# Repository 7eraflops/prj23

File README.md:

# 3-Phase 12-Channel ESP32 Energy Monitor

A custom ESP32-based energy meter measuring up to 12 channels across a 3-phase supply, integrated with Home Assistant via MQTT.

## Current Status
- End-to-end firmware flow is working on ESP32 DevKit: provisioning -> Wi-Fi -> MQTT -> HA discovery -> telemetry -> command handling.
- ATM90E32 real driver path is implemented (`register map`, `SPI transport`, `ATM90E32Sensor` implementing `IEnergySensor`).
- DevKit-only mock-IC path is implemented on a dedicated testing branch.
- Custom PCB and physical calibration are pending hardware availability.

## Overview
- **Measurement**: Uses the ATM90E32AS metering IC to monitor up to 12 circuits (11 used in current planned deployment).
- **Microcontroller**: ESP32-S3.
- **Integration**: Home Assistant MQTT Auto-Discovery for automatic entity configuration.
- **Provisioning**: Local captive portal and web server for Wi-Fi and MQTT setup.
- **Testing**: Uses mock sensor paths for software development before final hardware is available.

## Hardware
- **Custom PCB**: Currently in development.
- **MCU**: ESP32-S3
- **Metering IC**: ATM90E32AS
- **Sensors**: Current Transformers (CT Clamps) and Voltage Dividers

## Firmware Architecture
- `config_manager`: NVS-backed configuration (Wi-Fi, MQTT, channel phase assignment, active mask, calibration groundwork)
- `wifi_manager`: station lifecycle and reconnection
- `mqtt_manager`: client lifecycle, subscribe/publish, callback handling
- `ha_discovery`: Home Assistant discovery payload publishing
- `command_handler`: command topic handling and runtime config updates
- `sensor_manager`: polling task and telemetry publishing loop
- `atm90e32_interface`: register definitions, SPI transport, device abstraction
- `web_server`: provisioning/config pages and OTA endpoint

## Software Stack
- **Framework**: ESP-IDF (C/C++)
- **RTOS**: FreeRTOS
- **Communication**: MQTT (Mosquitto), HTTP (Local Web Server)
- **Data Processing**: Non-Intrusive Load Monitoring (NILM) runs server-side (Home Assistant / Raspberry Pi), not on the ESP32.

---

## Project Roadmap

### Phase 1: Software Foundation & HA Integration (Completed)
*Goal: Build the end-to-end data pipeline on the DevKit using mocked data before the physical hardware arrives.*

- [x] **Config & Provisioning (`config_manager`, `web_setup`)**
  - Save/load Wi-Fi and MQTT credentials using NVS.
  - Initial captive portal for device provisioning.
- [x] **MQTT Manager (`mqtt_manager`)**
  - Implement `esp_mqtt_client` using credentials from `config_manager`.
  - Handle connect/disconnect events and auto-reconnection logic.
- [x] **Home Assistant Auto-Discovery (`ha_discovery`)**
  - Implement HA MQTT Auto-Discovery protocol.
  - Publish JSON configuration payloads for Voltage, Current, Active Power, etc.
- [x] **Hardware Abstraction & Mock Sensor (`sensor_manager`)**
  - Define a generic sensor interface (`IEnergySensor`).
  - Create a `DummyEnergySensor` that generates fluctuating test data.
  - Implement a FreeRTOS telemetry task to poll the sensor and publish JSON payloads.

### Phase 2: Pre-Hardware System Features (Mostly Completed)
*Goal: Implement system-level features that can be tested on an ESP32 dev board before the custom PCBs arrive.*

- [x] **Continuous Web Server**
  - Keep web server active on the local network post-provisioning.
- [x] **Over-The-Air (OTA) Updates**
  - Implement OTA flashing mechanism.
  - Add an `/update` endpoint to the local web server to allow uploading firmware binaries.
- [x] **Two-Way MQTT Communication (Device Control)**
  - Add Home Assistant "Button" entities via HA Discovery (e.g., "Reboot").
  - Subscribe to command topics in `mqtt_manager` and execute device actions.
- [x] **Calibration Storage Groundwork**
  - Add NVS fields in `config_manager` for per-channel calibration settings.
- [X] **Calibration Web UI**
  - Add a `/calibration` web page to view and edit multipliers dynamically.

### Phase 3: Hardware Driver Preparation (In Progress)
*Goal: Write and validate the ATM90E32AS SPI driver path before custom hardware arrives.*

- [x] **ATM90E32AS Register Map**
  - Create header files defining register addresses and constants for status, calibration, instant values, power, and energy.
- [x] **SPI Interface**
  - Initialize the ESP32-S3 SPI master peripheral for shared bus + per-chip CS.
  - Implement low-level `read16()` and `write16()` functions and split-register 32-bit reads.
- [x] **ATM90E32 Sensor Implementation**
  - Create `ATM90E32Sensor` implementing `IEnergySensor`.
  - Integrate channel phase assignment and active mask behavior with existing runtime config.
- [x] **DevKit Mock IC Validation Path**
  - Add register-level ATM90E32 emulation path on testing branch to simulate fluctuating values and command/read flow.
- [ ] **Hardware Profile Finalization**
  - Finalize tuned mode/gain/threshold values when PCB and front-end are finalized.

### Phase 4: Hardware Bring-Up & Validation
*Goal: Validate the custom PCB and physically calibrate the sensors.*

- [X] **Physical Bring-Up**
  - Solder and power the PCB.
  - Validate SPI communication (e.g., read ATM90E32AS status/identity paths).
- [ ] **Live Calibration**
  - Connect actual loads and adjust multipliers via the Calibration Web UI.
  - Verify baseline noise and power factor readings.

### Phase 5: Non-Intrusive Load Monitoring (NILM)
*Goal: Differentiate multiple appliances sharing the same electrical circuit.*

#### ESP32 Responsibility (Data Provider)
The ESP32 acts as a high-fidelity data provider to Home Assistant. To aid in NILM separation, it publishes high-frequency updates (1-2 second intervals) per channel, including:
1. Active Power (W)
2. Reactive Power (var)
3. Apparent Power (VA)
4. Power Factor
5. Voltage (V) & Current (A)
6. Energy (kWh) & Frequency (Hz)
*(It also publishes device-level diagnostics like MCU temp, Wi-Fi RSSI, uptime, and free heap).*

#### Server Responsibility (Raspberry Pi 5 / Home Assistant)
Algorithms run on the server using Python (e.g., AppDaemon, custom HA integration, or NILMTK).

- [ ] **Circuit 1: Fridge (Compressor) + Coffee Maker (Resistive Heater)**
  - *Approach:* Step-Detection.
  - *Logic:* Detect flat active-power spikes (Coffee Maker) vs. reactive-power curves (Fridge). Subtract static loads to isolate devices.
- [ ] **Circuit 2: Washing Machine + Heat Pump Dryer**
  - *Approach:* State-Tracking ML Model (HMM / LSTM).
  - *Logic:* Train models on historical data to identify overlapping cycles based on combined Active and Reactive power footprints.

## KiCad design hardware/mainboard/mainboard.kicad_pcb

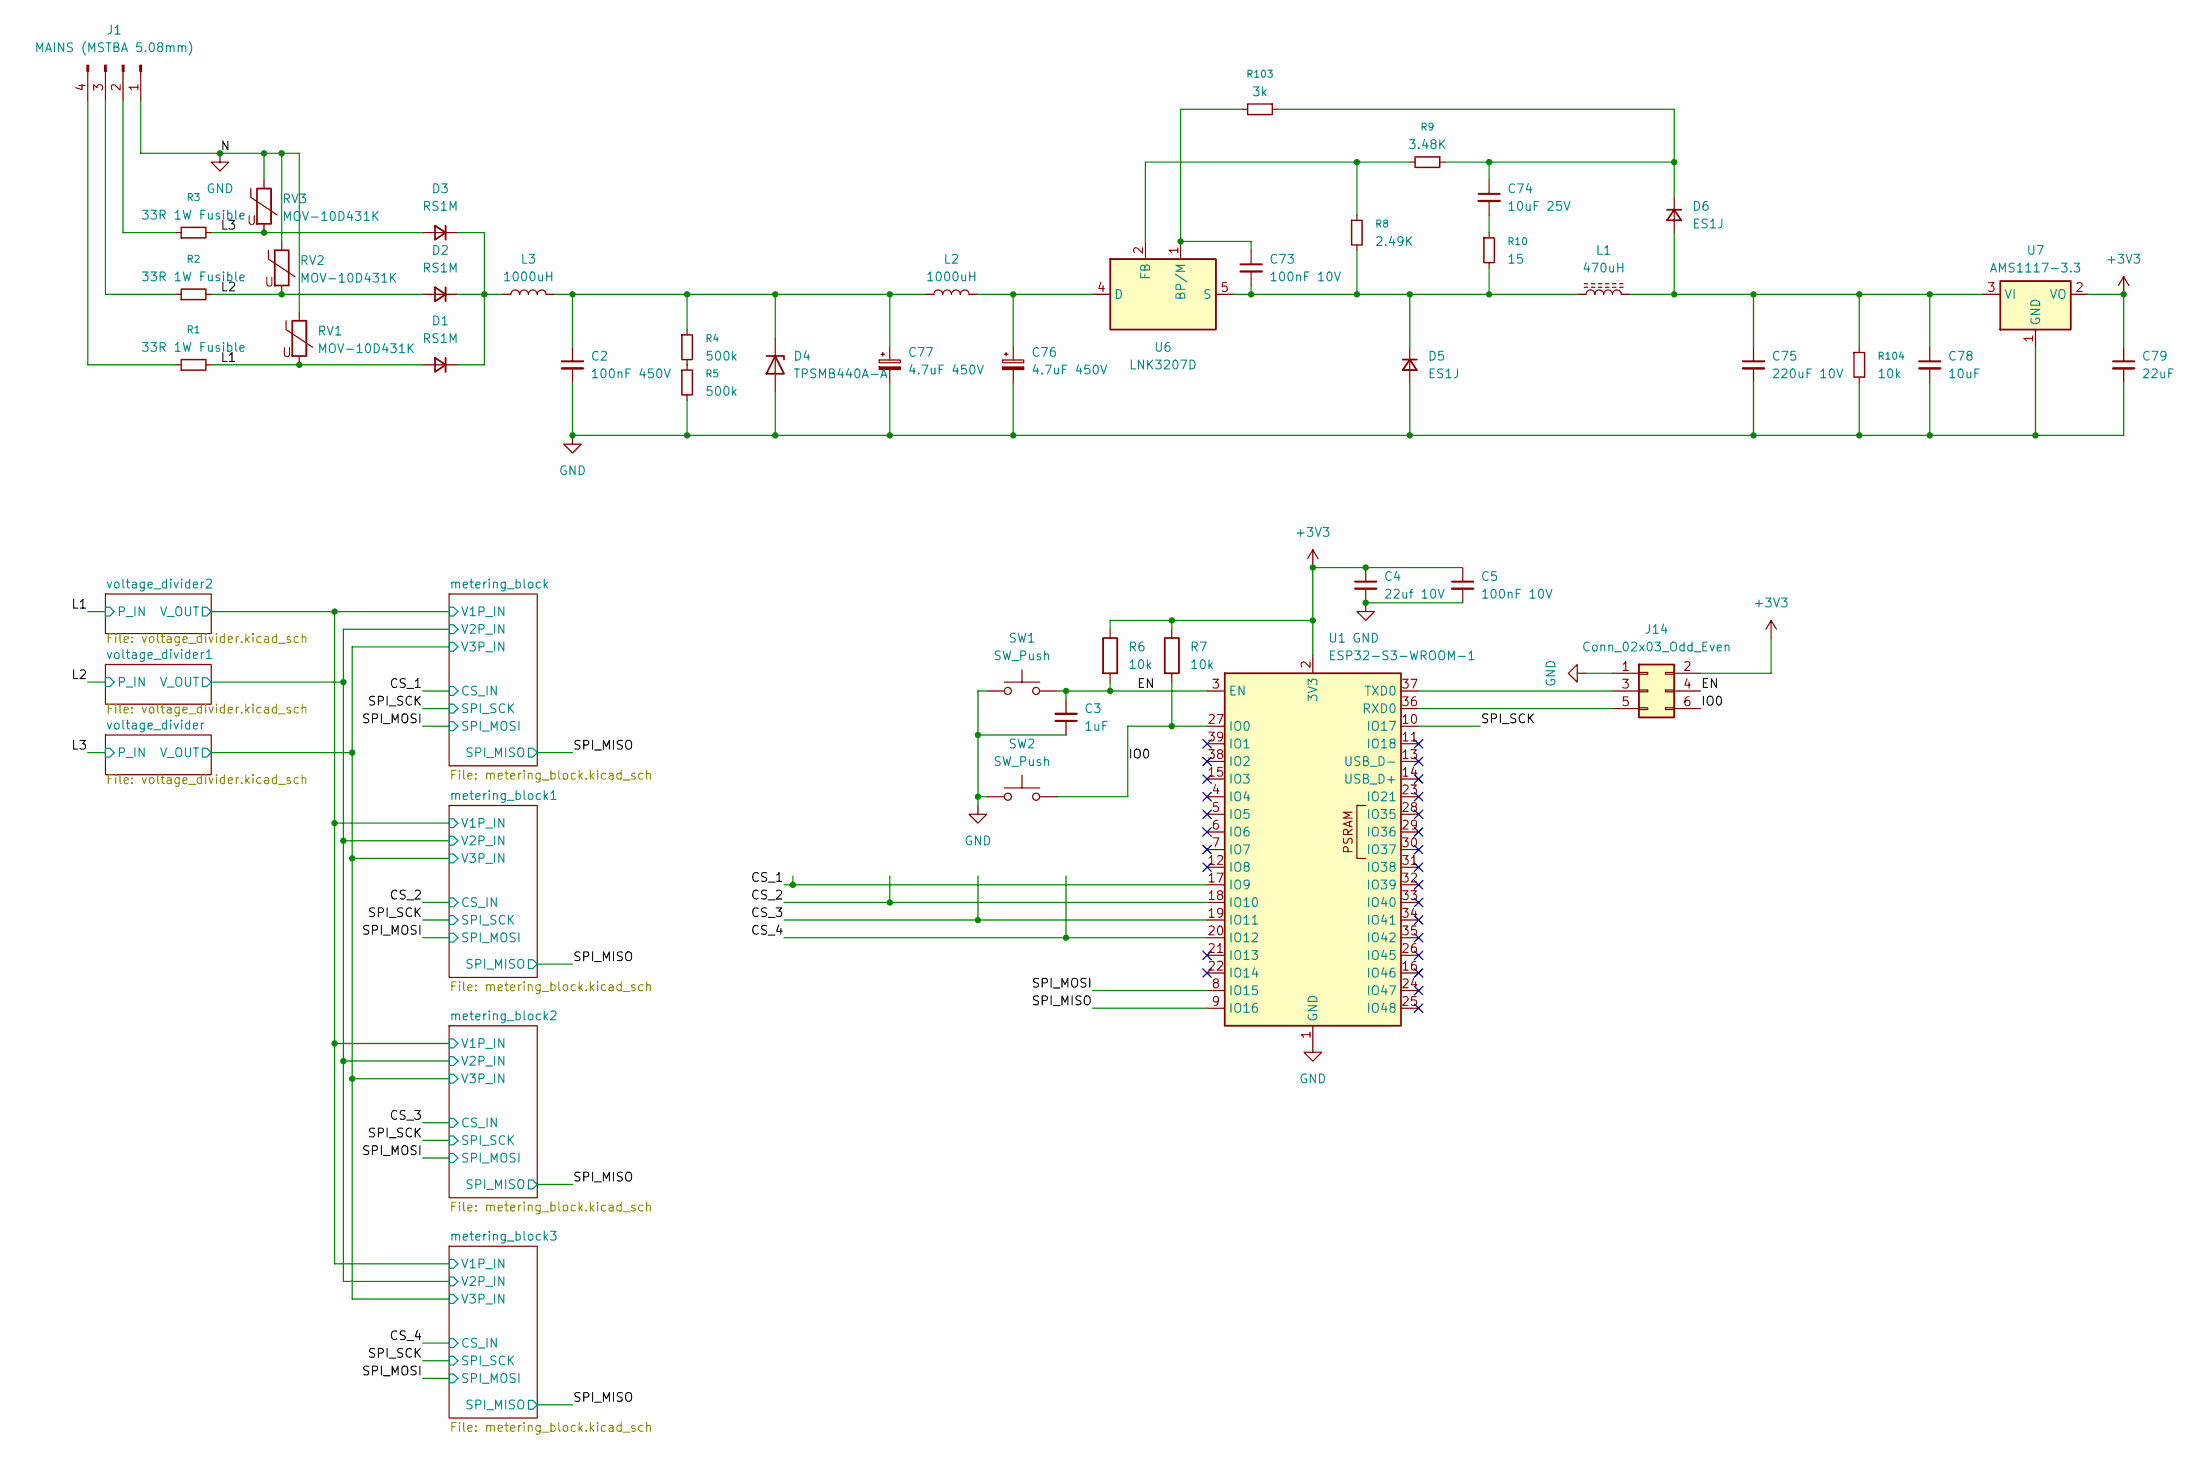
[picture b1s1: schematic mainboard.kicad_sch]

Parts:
C2: 100nF 450V; C_Rect_L13.0mm_W4.0mm_P10.00mm_FKS3_FKP3_MKS4
C3: 1uF; C_0603_1608Metric_Pad1.08x0.95mm_HandSolder
C4: 22uf 10V; C_1206_3216Metric_Pad1.33x1.80mm_HandSolder
C5, C73: 100nF 10V; C_0603_1608Metric_Pad1.08x0.95mm_HandSolder
C74: 10uF 25V; C_0805_2012Metric_Pad1.18x1.45mm_HandSolder
C75: 220uF 10V; CP_Radial_D6.3mm_P2.50mm
C76, C77: 4.7uF 450V; CP_Radial_D10.0mm_P5.00mm
C78: 10uF; C_0805_2012Metric_Pad1.18x1.45mm_HandSolder
C79: 22uF; C_0805_2012Metric_Pad1.18x1.45mm_HandSolder
D1, D2, D3: RS1M; D_SMA_Handsoldering
D4: TPSMB440A-A; D_SMB_Handsoldering
D5, D6: ES1J; D_SMA_Handsoldering
J1: MAINS (MSTBA 5.08mm); PhoenixContact_GMSTBA_2,5_4-G-7,62_1x04_P7.62mm_Horizontal
J14: Conn_02x03_Odd_Even; PinHeader_2x03_P2.54mm_Vertical
L1: 470uH; L_Bourns_SRR1208_12.7x12.7mm
L2, L3: 1000uH; L_6.3x6.3_H3
R1, R2, R3: 33R 1W Fusible; R_Axial_DIN0411_L9.9mm_D3.6mm_P12.70mm_Horizontal
R4, R5: 500k; R_1206_3216Metric_Pad1.30x1.75mm_HandSolder
R6, R7, R104: 10k; R_0603_1608Metric_Pad0.98x0.95mm_HandSolder
R8: 2.49K; R_0603_1608Metric_Pad0.98x0.95mm_HandSolder
R9: 3.48K; R_0603_1608Metric_Pad0.98x0.95mm_HandSolder
R10: 15; R_0603_1608Metric_Pad0.98x0.95mm_HandSolder
R103: 3k; R_0603_1608Metric_Pad0.98x0.95mm_HandSolder
RV1, RV2, RV3: MOV-10D431K; RV_Disc_D12mm_W5.4mm_P7.5mm
SW1, SW2: SW_Push; SW_Tactile_SPST_Angled_PTS645Vx58-2LFS
U1: ESP32-S3-WROOM-1
U6: LNK3207D; PowerIntegrations_SO-8C
U7: AMS1117-3.3; SOT-223-3_TabPin2

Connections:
/CS_1: U1.17 (IO9); also elsewhere on the board
/CS_2: U1.18 (IO10); also elsewhere on the board
/CS_3: U1.19 (IO11); also elsewhere on the board
/CS_4: U1.20 (IO12); also elsewhere on the board
/EN: C3.2, J14.4, R6.2, SW1.2, U1.3 (EN)
/IO0: J14.6, R7.2, SW2.2, U1.27 (IO0)
/L1: D1.2 (A), R1.2, RV1.2; also elsewhere on the board
/L2: D2.2 (A), R2.2, RV2.2; also elsewhere on the board
/L3: D3.2 (A), R3.2, RV3.2; also elsewhere on the board
/SPI_MISO: U1.9 (IO16); also elsewhere on the board
/SPI_MOSI: U1.8 (IO15); also elsewhere on the board
/SPI_SCK: U1.10 (IO17); also elsewhere on the board
GND: C2.2, C3.1, C4.2, C5.2, C75.2, C76.2, C77.2, C78.2, C79.2, D4.2 (A), D5.2 (A), J1.1, J14.1, R5.2, R104.2, RV1.1, RV2.1, RV3.1, SW1.1, SW2.1, U1.1 (GND), U1.40 (GND), U1.41 (GND), U7.1 (GND); also elsewhere on the board
unnamed: C74.2, R10.1
unnamed: D1.1 (K), D2.1 (K), D3.1 (K), L3.1
unnamed: C2.1, C77.1, D4.1 (K), L2.1, L3.2, R4.1
unnamed: C73.2, D5.1 (K), L1.1, R8.2, R10.2, U6.5 (S), U6.6 (S), U6.7 (S), U6.8 (S)
unnamed 44: C75.1, C78.1, D6.2 (A), L1.2, R104.1, U7.3 (VI); also elsewhere on the board
unnamed: C74.1, D6.1 (K), R9.1, R103.1
unnamed: J1.2, R3.1
unnamed: J1.3, R2.1
unnamed: J1.4, R1.1
unnamed: J14.3, U1.37 (TXD0)
unnamed: J14.5, U1.36 (RXD0)
unnamed: R4.2, R5.1
unnamed: C73.1, R103.2, U6.1 (BP/M)
unnamed: C76.1, L2.2, U6.4 (D)
unnamed: R8.1, R9.2, U6.2 (FB)

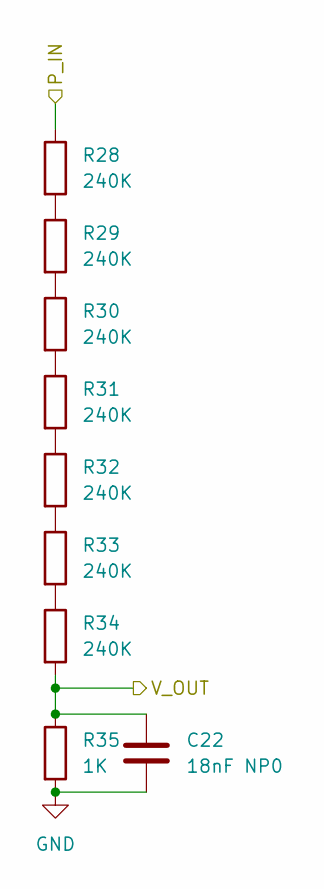
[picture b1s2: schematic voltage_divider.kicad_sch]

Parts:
C22: 18nF NP0; C_0603_1608Metric_Pad1.08x0.95mm_HandSolder
R28, R29, R30, R31, R32, R33, R34: 240K; R_0805_2012Metric_Pad1.20x1.40mm_HandSolder
R35: 1K; R_0603_1608Metric_Pad0.98x0.95mm_HandSolder

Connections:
/L3: R28.1; also elsewhere on the board
/metering_block/V3P_IN: C22.1, R34.2, R35.1; also elsewhere on the board
GND: C22.2, R35.2; also elsewhere on the board
unnamed: R28.2, R29.1
unnamed: R29.2, R30.1
unnamed: R30.2, R31.1
unnamed: R31.2, R32.1
unnamed: R32.2, R33.1
unnamed: R33.2, R34.1

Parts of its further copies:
C71, C72: 18nF NP0; C_0603_1608Metric_Pad1.08x0.95mm_HandSolder
R87, R88, R89, R90, R91, R92, R93, R95, R96, R97, R98, R99, R100, R101: 240K; R_0805_2012Metric_Pad1.20x1.40mm_HandSolder
R94, R102: 1K; R_0603_1608Metric_Pad0.98x0.95mm_HandSolder

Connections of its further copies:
/L1: R95.1; also elsewhere on the board
/L2: R87.1; also elsewhere on the board
/metering_block/V1P_IN: C72.1, R101.2, R102.1; also elsewhere on the board
/metering_block/V2P_IN: C71.1, R93.2, R94.1; also elsewhere on the board
GND: C71.2, C72.2, R94.2, R102.2; also elsewhere on the board
unnamed: R87.2, R88.1
unnamed: R88.2, R89.1
unnamed: R89.2, R90.1
unnamed: R90.2, R91.1
unnamed: R91.2, R92.1
unnamed: R92.2, R93.1
unnamed: R95.2, R96.1
unnamed: R96.2, R97.1
unnamed: R97.2, R98.1
unnamed: R98.2, R99.1
unnamed: R99.2, R100.1
unnamed: R100.2, R101.1

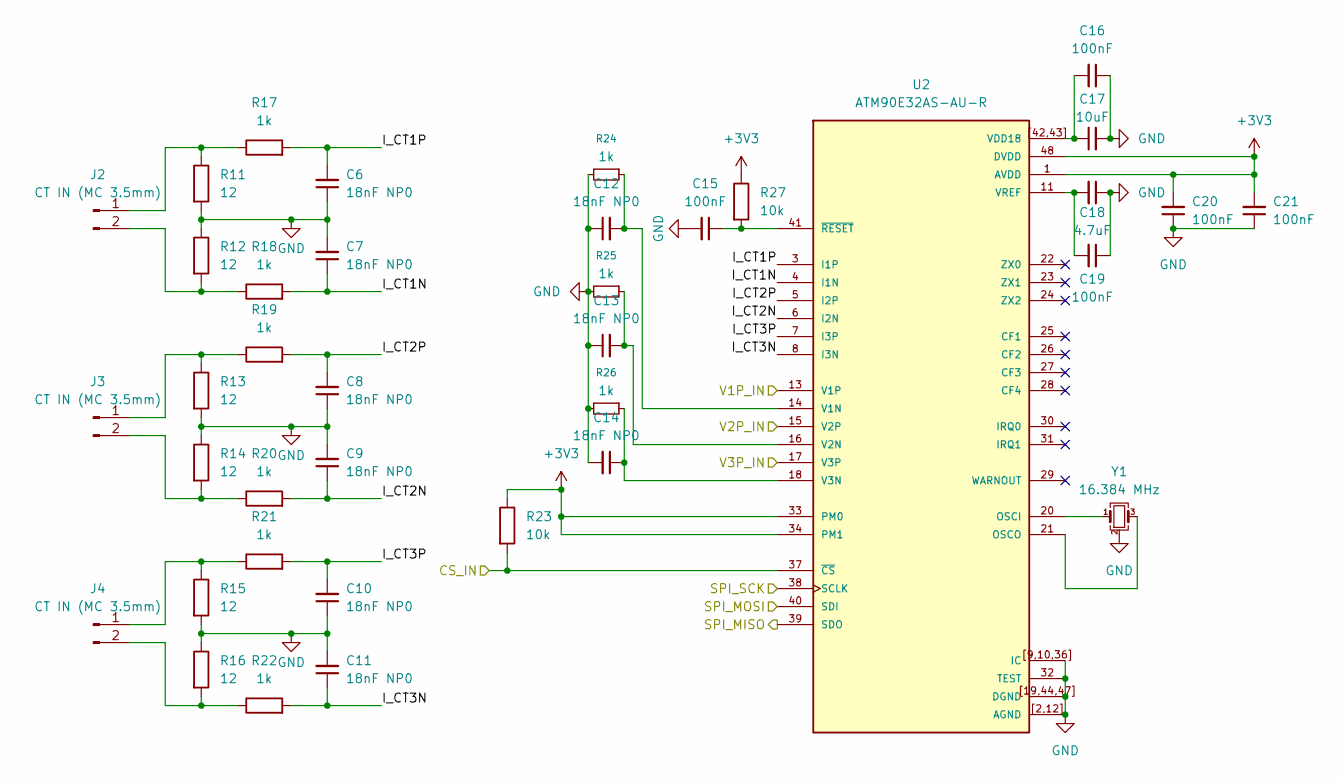
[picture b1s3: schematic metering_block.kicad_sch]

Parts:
C6, C7, C8, C9, C10, C11, C12, C13, C14: 18nF NP0; C_0603_1608Metric_Pad1.08x0.95mm_HandSolder
C15, C16, C19, C20, C21: 100nF; C_0603_1608Metric_Pad1.08x0.95mm_HandSolder
C17: 10uF; C_0805_2012Metric_Pad1.18x1.45mm_HandSolder
C18: 4.7uF; C_0805_2012Metric_Pad1.18x1.45mm_HandSolder
J2, J3, J4: CT IN (MC 3.5mm); PhoenixContact_MC_1,5_2-G-3.5_1x02_P3.50mm_Horizontal
R11, R12, R13, R14, R15, R16: 12; R_0603_1608Metric_Pad0.98x0.95mm_HandSolder
R17, R18, R19, R20, R21, R22, R24, R25, R26: 1k; R_0603_1608Metric_Pad0.98x0.95mm_HandSolder
R23, R27: 10k; R_0603_1608Metric_Pad0.98x0.95mm_HandSolder
U2: ATM90E32AS-AU-R; QFP50P900X900X120-48N; PARTREV 02/12/2015
Y1: 16.384 MHz; Crystal_SMD_3225-4Pin_3.2x2.5mm_HandSoldering

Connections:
/CS_1: R23.2, U2.37 (~CS); also elsewhere on the board
/SPI_MISO: U2.39 (SDO); also elsewhere on the board
/SPI_MOSI: U2.40 (SDI); also elsewhere on the board
/SPI_SCK: U2.38 (SCLK); also elsewhere on the board
/metering_block/I_CT1N: C7.1, R18.2, U2.4 (I1N)
/metering_block/I_CT1P: C6.2, R17.2, U2.3 (I1P)
/metering_block/I_CT2N: C9.1, R20.2, U2.6 (I2N)
/metering_block/I_CT2P: C8.2, R19.2, U2.5 (I2P)
/metering_block/I_CT3N: C11.1, R22.2, U2.8 (I3N)
/metering_block/I_CT3P: C10.2, R21.2, U2.7 (I3P)
/metering_block/V1P_IN: U2.13 (V1P); also elsewhere on the board
/metering_block/V2P_IN: U2.15 (V2P); also elsewhere on the board
/metering_block/V3P_IN: U2.17 (V3P); also elsewhere on the board
GND: C6.1, C7.2, C8.1, C9.2, C10.1, C11.2, C12.1, C13.1, C14.2, C15.2, C16.1, C17.2, C18.1, C19.1, C20.1, C21.1, R11.2, R12.1, R13.2, R14.1, R15.2, R16.1, R24.2, R25.2, R26.2, U2.2 (AGND), U2.9 (IC), U2.10 (IC), U2.12 (AGND), U2.19 (DGND), U2.32 (TEST), U2.36 (IC), U2.44 (DGND), U2.47 (DGND), U2.[2,12] (AGND), U2.[9,10,36] (IC), U2.[19,44,47] (DGND), Y1.2 (G), Y1.4 (G); also elsewhere on the board
unnamed: J2.1, R11.1, R17.1
unnamed: J2.2, R12.2, R18.1
unnamed: J3.1, R13.1, R19.1
unnamed: J3.2, R14.2, R20.1
unnamed: J4.1, R15.1, R21.1
unnamed: J4.2, R16.2, R22.1
unnamed: U2.20 (OSCI), Y1.1
unnamed: U2.21 (OSCO), Y1.3
unnamed: C12.2, R24.1, U2.14 (V1N)
unnamed: C13.2, R25.1, U2.16 (V2N)
unnamed: C14.1, R26.1, U2.18 (V3N)
unnamed: C16.2, C17.1, U2.42 (VDD18), U2.43 (VDD18), U2.[42,43] (VDD18)
unnamed: C18.2, C19.2, U2.11 (VREF)
unnamed: C15.1, R27.2, U2.41 (~RESET)

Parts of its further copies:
C23, C24, C25, C26, C27, C28, C29, C30, C31, C39, C40, C41, C42, C43, C44, C45, C46, C47, C55, C56, C57, C58, C59, C60, C61, C62, C63: 18nF NP0; C_0603_1608Metric_Pad1.08x0.95mm_HandSolder
C32, C33, C36, C37, C38, C48, C49, C52, C53, C54, C64, C65, C68, C69, C70: 100nF; C_0603_1608Metric_Pad1.08x0.95mm_HandSolder
C34, C50, C66: 10uF; C_0805_2012Metric_Pad1.18x1.45mm_HandSolder
C35, C51, C67: 4.7uF; C_0805_2012Metric_Pad1.18x1.45mm_HandSolder
J5, J6, J7, J8, J9, J10, J11, J12, J13: CT IN (MC 3.5mm); PhoenixContact_MC_1,5_2-G-3.5_1x02_P3.50mm_Horizontal
R36, R37, R38, R39, R40, R41, R53, R54, R55, R56, R57, R58, R70, R71, R72, R73, R74, R75: 12; R_0603_1608Metric_Pad0.98x0.95mm_HandSolder
R42, R43, R44, R45, R46, R47, R49, R50, R51, R59, R60, R61, R62, R63, R64, R66, R67, R68, R76, R77, R78, R79, R80, R81, R83, R84, R85: 1k; R_0603_1608Metric_Pad0.98x0.95mm_HandSolder
R48, R52, R65, R69, R82, R86: 10k; R_0603_1608Metric_Pad0.98x0.95mm_HandSolder
U3, U4, U5: ATM90E32AS-AU-R; QFP50P900X900X120-48N; PARTREV 02/12/2015
Y2, Y3, Y4: 16.384 MHz; Crystal_SMD_3225-4Pin_3.2x2.5mm_HandSoldering

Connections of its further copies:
/CS_2: R48.2, U3.37 (~CS); also elsewhere on the board
/CS_3: R65.2, U4.37 (~CS); also elsewhere on the board
/CS_4: R82.2, U5.37 (~CS); also elsewhere on the board
/SPI_MISO: U3.39 (SDO), U4.39 (SDO), U5.39 (SDO); also elsewhere on the board
/SPI_MOSI: U3.40 (SDI), U4.40 (SDI), U5.40 (SDI); also elsewhere on the board
/SPI_SCK: U3.38 (SCLK), U4.38 (SCLK), U5.38 (SCLK); also elsewhere on the board
/metering_block1/I_CT1N: C24.1, R43.2, U3.4 (I1N)
/metering_block1/I_CT1P: C23.2, R42.2, U3.3 (I1P)
/metering_block1/I_CT2N: C26.1, R45.2, U3.6 (I2N)
/metering_block1/I_CT2P: C25.2, R44.2, U3.5 (I2P)
/metering_block1/I_CT3N: C28.1, R47.2, U3.8 (I3N)
/metering_block1/I_CT3P: C27.2, R46.2, U3.7 (I3P)
/metering_block2/I_CT1N: C40.1, R60.2, U4.4 (I1N)
/metering_block2/I_CT1P: C39.2, R59.2, U4.3 (I1P)
/metering_block2/I_CT2N: C42.1, R62.2, U4.6 (I2N)
/metering_block2/I_CT2P: C41.2, R61.2, U4.5 (I2P)
/metering_block2/I_CT3N: C44.1, R64.2, U4.8 (I3N)
/metering_block2/I_CT3P: C43.2, R63.2, U4.7 (I3P)
/metering_block3/I_CT1N: C56.1, R77.2, U5.4 (I1N)
/metering_block3/I_CT1P: C55.2, R76.2, U5.3 (I1P)
/metering_block3/I_CT2N: C58.1, R79.2, U5.6 (I2N)
/metering_block3/I_CT2P: C57.2, R78.2, U5.5 (I2P)
/metering_block3/I_CT3N: C60.1, R81.2, U5.8 (I3N)
/metering_block3/I_CT3P: C59.2, R80.2, U5.7 (I3P)
/metering_block/V1P_IN: U3.13 (V1P), U4.13 (V1P), U5.13 (V1P); also elsewhere on the board
/metering_block/V2P_IN: U3.15 (V2P), U4.15 (V2P), U5.15 (V2P); also elsewhere on the board
/metering_block/V3P_IN: U3.17 (V3P), U4.17 (V3P), U5.17 (V3P); also elsewhere on the board
GND: C23.1, C24.2, C25.1, C26.2, C27.1, C28.2, C29.1, C30.1, C31.2, C32.2, C33.1, C34.2, C35.1, C36.1, C37.1, C38.1, C39.1, C40.2, C41.1, C42.2, C43.1, C44.2, C45.1, C46.1, C47.2, C48.2, C49.1, C50.2, C51.1, C52.1, C53.1, C54.1, C55.1, C56.2, C57.1, C58.2, C59.1, C60.2, C61.1, C62.1, C63.2, C64.2, C65.1, C66.2, C67.1, C68.1, C69.1, C70.1, R36.2, R37.1, R38.2, R39.1, R40.2, R41.1, R49.2, R50.2, R51.2, R53.2, R54.1, R55.2, R56.1, R57.2, R58.1, R66.2, R67.2, R68.2, R70.2, R71.1, R72.2, R73.1, R74.2, R75.1, R83.2, R84.2, R85.2, U3.2 (AGND), U3.9 (IC), U3.10 (IC), U3.12 (AGND), U3.19 (DGND), U3.32 (TEST), U3.36 (IC), U3.44 (DGND), U3.47 (DGND), U4.2 (AGND), U4.9 (IC), U4.10 (IC), U4.12 (AGND), U4.19 (DGND), U4.32 (TEST), U4.36 (IC), U4.44 (DGND), U4.47 (DGND), U5.2 (AGND), U5.9 (IC), U5.10 (IC), U5.12 (AGND), U5.19 (DGND), U5.32 (TEST), U5.36 (IC), U5.44 (DGND), U5.47 (DGND), Y2.2 (G), Y2.4 (G), Y3.2 (G), Y3.4 (G), Y4.2 (G), Y4.4 (G); also elsewhere on the board
unnamed: J5.1, R36.1, R42.1
unnamed: J5.2, R37.2, R43.1
unnamed: J6.1, R38.1, R44.1
unnamed: J6.2, R39.2, R45.1
unnamed: J7.1, R40.1, R46.1
unnamed: J7.2, R41.2, R47.1
unnamed: J8.1, R53.1, R59.1
unnamed: J8.2, R54.2, R60.1
unnamed: J9.1, R55.1, R61.1
unnamed: J9.2, R56.2, R62.1
unnamed: J10.1, R57.1, R63.1
unnamed: J10.2, R58.2, R64.1
unnamed: J11.1, R70.1, R76.1
unnamed: J11.2, R71.2, R77.1
unnamed: J12.1, R72.1, R78.1
unnamed: J12.2, R73.2, R79.1
unnamed: J13.1, R74.1, R80.1
unnamed: J13.2, R75.2, R81.1
unnamed: U3.20 (OSCI), Y2.1
unnamed: U3.21 (OSCO), Y2.3
unnamed: C29.2, R49.1, U3.14 (V1N)
unnamed: C30.2, R50.1, U3.16 (V2N)
unnamed: C31.1, R51.1, U3.18 (V3N)
unnamed: C33.2, C34.1, U3.42 (VDD18), U3.43 (VDD18)
unnamed: C35.2, C36.2, U3.11 (VREF)
unnamed: C32.1, R52.2, U3.41 (~RESET)
unnamed: U4.20 (OSCI), Y3.1
unnamed: U4.21 (OSCO), Y3.3
unnamed: C45.2, R66.1, U4.14 (V1N)
unnamed: C46.2, R67.1, U4.16 (V2N)
unnamed: C47.1, R68.1, U4.18 (V3N)
unnamed: C49.2, C50.1, U4.42 (VDD18), U4.43 (VDD18)
unnamed: C51.2, C52.2, U4.11 (VREF)
unnamed: C48.1, R69.2, U4.41 (~RESET)
unnamed: U5.20 (OSCI), Y4.1
unnamed: U5.21 (OSCO), Y4.3
unnamed: C61.2, R83.1, U5.14 (V1N)
unnamed: C62.2, R84.1, U5.16 (V2N)
unnamed: C63.1, R85.1, U5.18 (V3N)
unnamed: C65.2, C66.1, U5.42 (VDD18), U5.43 (VDD18)
unnamed: C67.2, C68.2, U5.11 (VREF)
unnamed: C64.1, R86.2, U5.41 (~RESET)

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
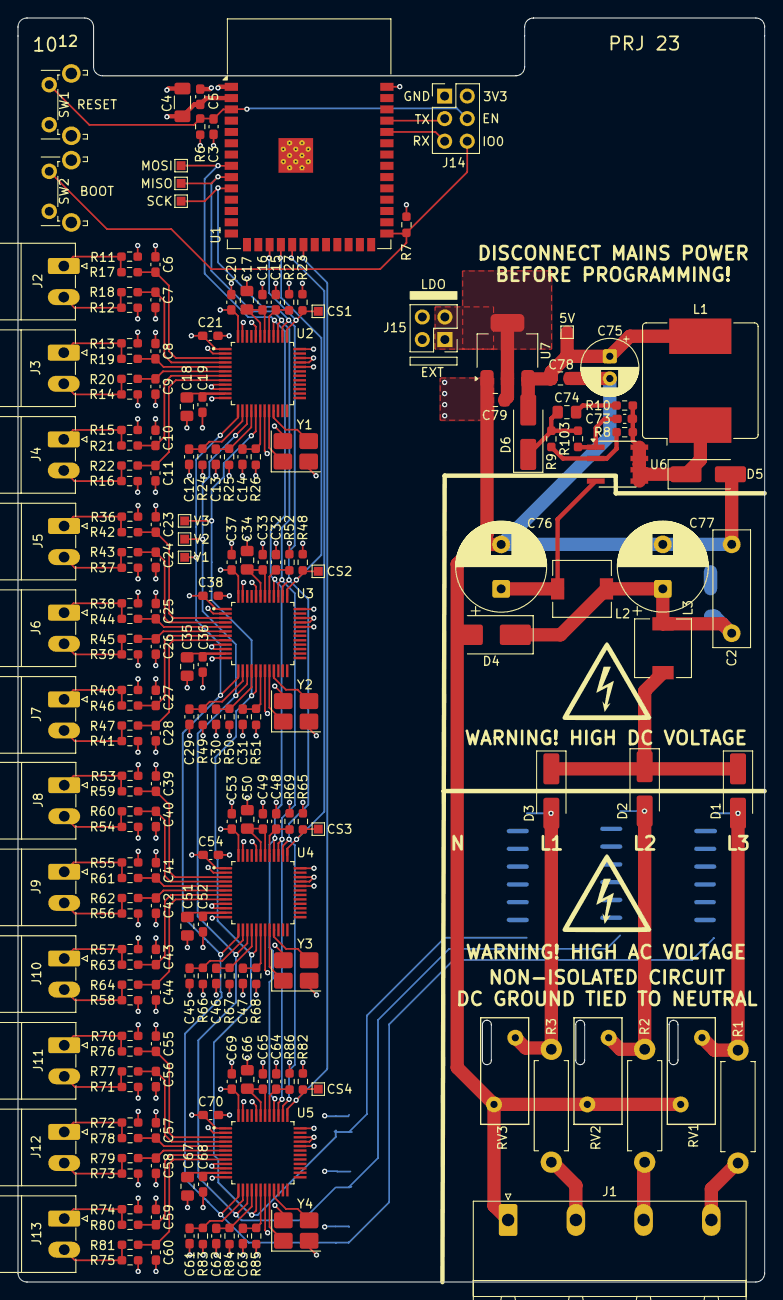
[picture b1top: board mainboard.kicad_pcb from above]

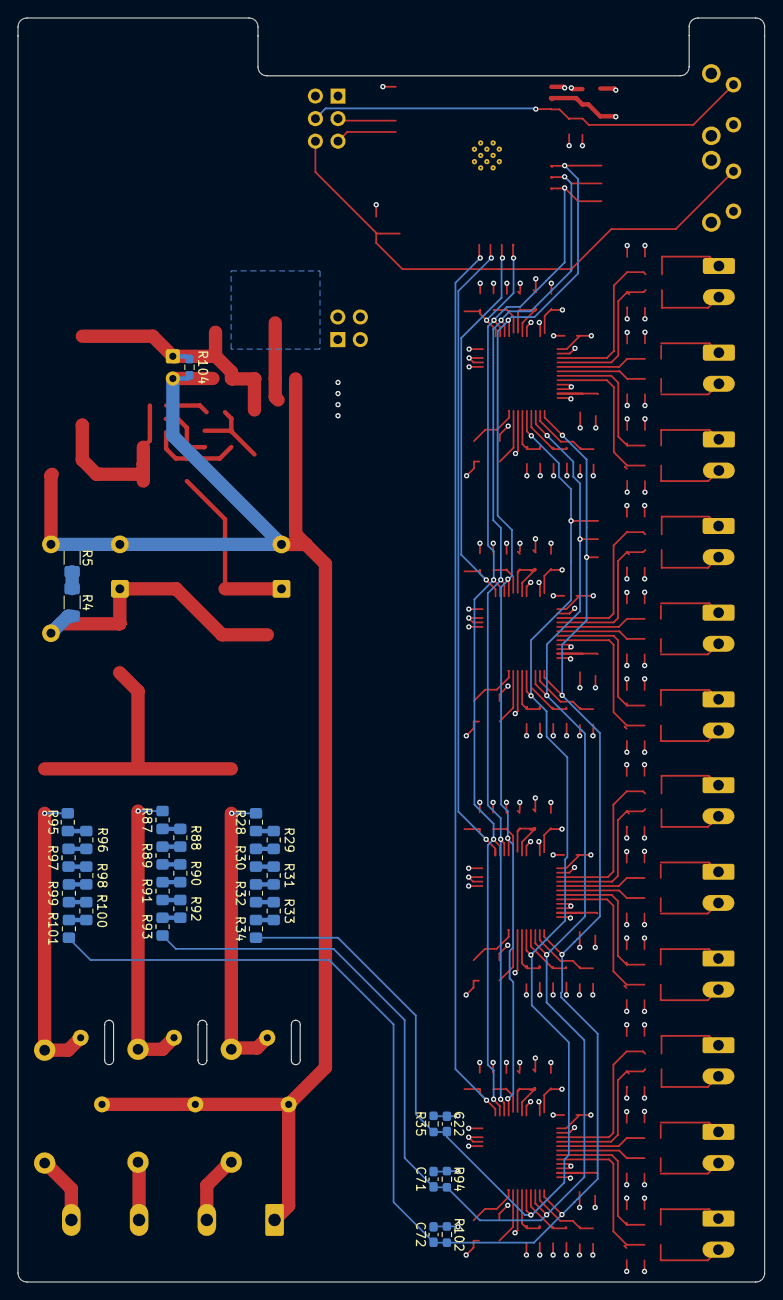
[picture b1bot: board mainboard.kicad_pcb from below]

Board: 4 copper layers, 84.0 x 142.2 mm, 233 parts (30 on the bottom side), 131 nets.

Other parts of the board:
J15: Conn_02x02_Odd_Even; PinHeader_2x02_P2.54mm_Vertical
TP1: V1; TestPoint_Pad_1.0x1.0mm
TP2: V2; TestPoint_Pad_1.0x1.0mm
TP3: V3; TestPoint_Pad_1.0x1.0mm
TP4: CS1; TestPoint_Pad_1.0x1.0mm
TP5: CS2; TestPoint_Pad_1.0x1.0mm
TP6: CS3; TestPoint_Pad_1.0x1.0mm
TP7: CS4; TestPoint_Pad_1.0x1.0mm
TP8: SCK; TestPoint_Pad_1.0x1.0mm
TP9: MOSI; TestPoint_Pad_1.0x1.0mm
TP10: MISO; TestPoint_Pad_1.0x1.0mm
TP11: 5V; TestPoint_Pad_1.0x1.0mm

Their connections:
/CS_1: TP4.1 (1_1); also elsewhere on the board
/CS_2: TP5.1 (1_1); also elsewhere on the board
/CS_3: TP6.1 (1_1); also elsewhere on the board
/CS_4: TP7.1 (1_1); also elsewhere on the board
/SPI_MISO: TP10.1 (1_1); also elsewhere on the board
/SPI_MOSI: TP9.1 (1_1); also elsewhere on the board
/SPI_SCK: TP8.1 (1_1); also elsewhere on the board
/metering_block/V1P_IN: TP1.1 (1_1); also elsewhere on the board
/metering_block/V2P_IN: TP2.1 (1_1); also elsewhere on the board
/metering_block/V3P_IN: TP3.1 (1_1); also elsewhere on the board
unnamed 44: TP11.1 (1_1); also elsewhere on the board

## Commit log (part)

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2026-03-16 Initial commit
    add .gitignore and README.md
2026-03-23 chore: update gitignore for editor and esp-idf cache files
    - Ignore .clangd and .zed/ to keep local editor configs out of version
    control
    - Ignore ESP-IDF generated files: firmware/.cache/ and
    firmware/sdkconfig
    - Ensure compile_commands.json remains ignored as it contains absolute
    paths
2026-03-23 build: add local clangd generation script for esp-idf
    - Adds a Bash script to dynamically generate a .clangd file.
    - Automatically extracts the local Xtensa GCC system include paths.
    - Resolves 'string file not found' and 'std undeclared' LSP errors.
    - Keeps machine-specific absolute paths out of version control.
2026-03-24 feat(config): add ConfigManager for NVS credential persistence
    - Implements loading and saving of configuration via ESP-IDF NVS.
    - Persists user-provided Wi-Fi SSID, password, and MQTT details.
    - Defines clear() to wipe all persistent application settings.
2026-03-24 feat(mdns): add auto-discovery for MQTT and WebSocket brokers
    - Adds mdns_manager component to announce the setup UI on 'energy-meter.local'.
    - Auto-discovers local MQTT services to pre-fill the frontend form.
    - Infers MQTT protocol (ws:// vs mqtt://) from TXT records.
    - Refreshes mDNS announcements transparently when switching IP networks.
2026-03-24 refactor(wifi): replace app provisioning with raw AP/STA management
    - Rewrites WifiManager to cleanly handle AP, STA, and APSTA modes.
    - Supports maintaining a connection to clients while testing router credentials.
    - Adds functionality to clear saved Wi-Fi credentials.
    - Exposes get_sta_ip() method to retrieve the station IP address.
    - Removes old ESP-IDF app-based provisioning logic.
2026-03-24 feat(setup): implement embedded web UI for device and MQTT provisioning
    - Implements a lightweight HTTP web server using esp_http_server.
    - Serves a bundled, single-file TypeScript/HTML frontend.
    - Provides REST endpoints to scan Wi-Fi, save settings, and reboot.
    - Adds auto-redirect capability upon successful network association.
2026-03-24 build: update gitignore for web frontend build artifacts
2026-03-24 feat(main): orchestrate new web setup flow and component lifecycle
    - Replaces old setup execution with conditional Setup Portal initialization.
    - Relocates main.cpp into a src/ directory for structural consistency.
    - Wires up ConfigManager to load settings on boot.
    - Instantiates MdnsManager and BoardManager.
2026-03-24 feat(ha): implement MQTT Auto-Discovery for Home Assistant
    - Create `HaDiscovery` component to generate Home Assistant config payloads
    - Configure 12 individual channels as sub-devices via `via_device`
    - Expose V, A, W, VA, VAR, PF, Hz, and kWh per channel
    - Add device diagnostic sensors (Uptime, Free Heap, Wi-Fi RSSI, MCU Temp)
    - Add MCU temperature sensor initialization to `board_manager`
    - Link sensor availability to device heartbeat payload
2026-03-25 docs: add roadmap to README.md
2026-03-25 chore: add private_include directory to sensor_manager
    This directory is required by CMakeLists.txt as PRIV_INCLUDE_DIRS. It will house private headers for concrete sensor implementations (like dummy_sensor and the future ATM90E32 driver) that do not nee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
2026-03-26 docs: update Phase 2 roadmap in README.md
2026-03-26 feat(wifi): update behavior post-setup
    Adds set_mode method to WifiManager and updates connect() to respect the current mode. This allows explicitly disabling the Access Point (AP) when the device is already configured, transitionining to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
2026-03-26 feat(web): implement tabbed management interface
    Introduces a tabbed UI for Wi-Fi and MQTT configuration. The interface automatically adapts between a linear setup wizard for unconfigured devices and a tabbed management view for configured ones, fe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
2026-03-26 feat(main): enable persistent web server and AP management
    Refactors app_main to ensure the web server is always active for local management. When a configuration is present, the device now explicitly disables the Access Point by switching to STA mode before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
2026-03-26 cleanup: remove the redundant index.html
2026-03-27 chore(build): use PRIV_REQUIRES for main component dependencies
2026-03-27 chore: allow tracking partitions.csv in gitignore
    Moves the partitions.csv exception to the ESP-IDF section and ensures it is not ignored by the broad KiCad CSV rule.
2026-03-27 feat(ota): configure 8MB flash and custom partition table
    Updates the project to target 8MB flash modules and introduces a custom partition table with dual 3MB OTA slots and a 1MB storage partition. This is required for reliable A/B firmware updates.
2026-03-28 refactor(web): separate CSS from index.html
    Moves embedded CSS into a dedicated style.css file in the source directory. The build script has been updated to inline the CSS during the build process, maintaining a single-file deployment while im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
2026-03-28 refactor: move OTA update logic to a dedicated ota_manager component
    Encapsulates ESP-IDF OTA operations into a reusable component. This
    decouples the firmware update process from the web server implementation
    and improves overall system modularity.
2026-03-28 style: apply clang-format to entire codebase
2026-03-29 build: set explicit target and upgrade to C++26
2026-03-29 style: update clang-format standard to C++26
2026-03-29 build(board_manager): update driver requirements for ESP-IDF 6.0
2026-03-29 build(mqtt_manager): migrate to modular managed MQTT
2026-03-29 build: remove unused provisioning symbols
2026-03-30 feat(mqtt): add LWT and discovery throttling
2026-03-30 feat(web_server): add input length validation to save handler
2026-03-30 refactor(config,mqtt): add mutex protection to shared managers
2026-03-31 feat(diagnostics): format uptime as human-readable and add stack monitoring to heartbeat
2026-03-31 refactor(board): replace reset button polling with GPIO interrupt
    - Eliminates the InputContext memory leak by removing heap allocation entirely. All state is now static globals.
    - Replaces the dedicated 4KB-stack FreeRTOS polling task with a lightweight GPIO ISR + ESP timer. The ISR arms a one-shot timer on button press (falling edge) and disarms it on release (rising edge).
    - Adds graceful shutdown before reboot: stops MQTT, shuts down WiFi, then clears NVS and restarts.
2026-03-31 feat(config_manager): add channel active states and phase assignments to NVS
    - Add channel_active_mask (bitmask) and channel_phases[12] array to AppConfig.
    - Default phase assignment: channels 1-4 = Phase A, 5-8 = Phase B, 9-12 = Phase C.
    - Add NVS persistence for channel settings via save_channel_settings().
    - Add getters/setters for per-channel active state and phase assignment.
2026-03-31 feat(ha_discovery): add control entities for device management
    - Add button entities: Reboot, Factory Reset (disabled by default), WiFi Reconnect, Republish Discovery.
    - Add 12 switch entities for per-channel active/inactive control (Controls section).
    - Add 12 select entities for per-channel phase assignment (Phase A/B/C/None).
    - Add configuration_url pointing to http://energy-meter.local for the Visit device link.
    - Remove Free Heap and Stack High Watermark diagnostic sensors — not useful.
    - All entities publish to the main ESP32 Energy Meter device with availability via heartbeat.
2026-03-31 feat(main): wire up command handler and MQTT subscriptions
    - Register command_handler component in build.
    - Connect MQTT on_message callback to command handler queue.
    - Trigger discovery republish and state publishing on MQTT connect/reconnect.
2026-04-01 Docs: Update Roadmap
2026-04-12 feat(atm90e32): add multi-chip ATM90E32 sensor backend
    Introduce an ATM90E32 interface component with register definitions, SPI transport, and per-chip device reads for 4 chips on a shared SPI bus.\nIntegrate the new backend with SensorManager and app st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
2026-04-12 feat(config,mqtt): persist calibration settings and fix callback deadlock
    Add per-channel calibration storage in NVS to prepare channel-level ATM90E32 tuning without changing runtime schemas.\nRefactor MQTT callback execution to run outside internal locks so discovery and 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
2026-04-12 Docs: Update roadmap for ATM90E32 integration progress
    Reflect completed Phase 3 driver work, calibration storage groundwork, and the dedicated mock ATM90E32 testing path used on DevKit before hardware arrives.\nClarify remaining Phase 2/3 items so next 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
2026-04-19 Add first iteration of project report
2026-05-04 Add PCB layout
2026-05-07 hw: Separate 1 IC + 3 CT inputs into a subschematic for cleanliness
2026-05-07 hw: Separate 1 voltage divider into subschematic for cleanliness
2026-05-07 hw: Add 5V buck regulator
2026-05-07 hw: Redo HV section layout
2026-05-07 hw: Add LDO and GND/3V3 traces
2026-05-07 hw: Complete final(?) board design
2026-05-07 hw: Finalize PCB design
2026-06-09 fix(spi): correct GPIO pin mapping and byte order in transfer16
2026-06-09 calibration: set default U/I gain values for 50Hz mode
    Set initial calibration constants for voltage gain (0xC7CE) and
    current gain (0x27A4 for all 3 phases) along with line frequency
    mode (0x0185). These are starting defaults and will be refined
    through further calibration.
2026-06-09 fix(phase): align phase labels with PCB (L1/L2/L3) and correct voltage mapping
    The schematic cross-wires voltage inputs: V1P=L3, V2P=L2, V3P=L1.
    Previously PHASE_A mapped to Line A (V1P = L3), so L1 voltage appeared
    on channels 9-12 instead of channels 1-4.
    Changes:
    - Rename ChannelPhase enum: PHASE_A/B/C -> PHASE_L1/L2/L3
    - Swap L1/L3 in phase_to_input: L1 -> Line C (V3P), L2 -> Line B (V2P),
2026-06-13 docs(readme): update project status
    Mark the following tasks as completed:
    - Calibration Web UI
    - Physical Bring-Up
2026-06-17 feat(config): add hardware calibration blob storage via NVS
    - Introduce CalibrationData struct within AppConfig containing all
    ATM90E32 calibration parameters (gains, offsets, thresholds, phase
    angles, power constant, PGA mode, line frequency).
    - Persist CalibrationData as a binary blob in NVS under the 'hw_cal' key.
    - Add getter/setter and save_hardware_calibration() for programmatic
    access.
2026-06-17 feat(sensor): integrate hardware calibration and fix phase-to-input mapping
    - Read CalibrationData from ConfigManager at init and map it to the
    per-chip DeviceConfig, supporting per-channel calibration (gain,
    offset, phase angle) across all 12 channels (4 chips × 3 phases).
    - Configure line frequency mode (50/60 Hz) and PGA gain from
    calibration data instead of hard-coded values.
    - Correct phase_to_input() mapping: L1→A, L2→B, L3→C (was wrongly
2026-06-17 feat(web): add calibration REST API (GET/PUT /api/calibration)
    - Add GET /api/calibration handler that serializes the full
    CalibrationData (hardware calibration) plus per-channel energy
    offsets as JSON.
    - Add PUT /api/calibration handler that deserializes the JSON payload,
    applies it to the running config, and persists via ConfigManager.
    - Register both handlers and bump max_uri_handlers from 10 to 12.
2026-06-18 fix(main): add atm90e32_interface dependency to main component
2026-06-18 feat(main): add human-readable uptime to heartbeat payload
2026-06-18 feat(wifi): add exponential backoff for reconnect attempts
2026-06-18 refactor(sensor_manager): improve sensor interfaces and move atm90e32_sensor
2026-06-18 refactor(config): improve config manager serialization
